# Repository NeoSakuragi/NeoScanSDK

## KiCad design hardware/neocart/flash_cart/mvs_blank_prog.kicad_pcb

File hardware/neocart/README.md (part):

# NeoCart — status 2026-10-01

Single entry point for the cartridge hardware. The 2026-09-23 status further down is kept as history.

## Plan (decided)
- **NeoCart = a platform for homebrews.** Protected commercial games (KOF2000-class: SMA, PVC, PCM2 encryption) are out of scope for now.
- **Flash carts are how games ship; a separate programmer writes them.** The FPGA + RAM cart (NeoSD/Darksoft style) stays a later **dev-cart** track
  (instant reload, bus tracing, breakpoints), not the production cart.
- **Programming is NOT embedded on the cart** (comparison in `progr/DESIGN.md`): ~+$56 per 2-cart order (MCU parts, 6 extended-part fees,
  4 layers), an MCU wired to every flash pin on the live bus, no dump/bench capability. The separate programmer is paid once and doubles as a
  dumper / bench tool, and may be sold later.

## Boards
| Board | Folder | State |
|---|---|---|
| **PROG board v3** (CTRG2) | `pboard/` | Routed, DRC 0/0, Gerbers/BOM/CPL exported. 174 × 134 mm, 2 layers, HASL fingers. P = S29GL064N (8 MB, P1 at MB 7, P2 bank n at MB n, 3-bit latch at $2FFFF0); V = ONE S29GL128P shared by ADPCM-A and ADPCM-B (LVC16374 capture registers as a tri-state mux, break-before-make on /SDPOE). JP1: 1-2 PROGRAM / 2-3 PLAY. Logic sim `sim_pboard.py` 14/14. JLCPCB project "neocart_pboard_jlcpcb": 5 PCBs + 2 assembled = **$94.90** before shipping (real quote). **Not ordered.** |
| **Programmer v1** | `progr/` | Routed, DRC 0/0, exported. 176 × 100 mm, 2 layers. WeAct RP2350B core board on headers + MVS slot (EDAC 345-120-520-201) + 4 × SN74LVC16T245, 74LVC16245A (D bus at 3.3 V), 2 × 74LVC16374 latches, TPS2553 cart switch. Netlist imports the CTRG2 table from `pboard/`; `sim_system.py` runs the firmware cycles against the PROG board netlist (9/9, 6 planted faults caught). Firmware `progr/firmware` (Pico SDK, UF2 in `progr/out`), PC tool `progr/neocart.py`. JLCPCB project "neocart_progr_jlcpcb": 5 PCBs + 2 assembled ≈ **$59** before shipping (built from JLCPCB's own BOM prices; final page not read). Plus module ~$4 and slot ~$14-19 bought separately. **Not ordered.** |
| CHA board | — | Not designed. Reference: KOF96 CHA256 (NEO-273 address latch, NEO-ZMC, 8 × 4 MB C, AT27C010 S1/M1). Will be designed together with programmer v2 (two slots, second WeAct module). |

## Before ordering
1. **Logic-analyzer capture** of /SDROE (A56), /SDPOE (A48), SDRMPX (A55), SDPMPX (A47) on Bruno's MVS with KOF96 playing music: the v3 PROG
   board's one unproven assumption (neogeodev wiki: the two strobes fall together, /SDPOE 250 ns, /SDROE 1.5 µs). Tool: any FX2 "24MHz 8CH"
   USB analyzer (CY7C68013A, sigrok/PulseView), ~€16; the Kingst LA1010 (€72) adds nothing needed here. A probe map (where the four lines run on
   the KOF96 PROG board) is still to be made from the scans.
2. **1:1 paper print** of the PROG board in a real shell (fit).
3. Order both boards in ONE JLCPCB order (one wait, one shipment).
Bring-up order: programmer first, validated by dumping Bruno's own SNK carts against MAME CRCs; then the PROG board, debugged with it.

## Reference hardware
`/data/scans/kof96/` (README + photos): 600 dpi scans and phone photos of KOF96 PROGBK1 and CHA256. PROGBK1 confirms our PROG outline
(holes 90.0 mm apart, 103.7 mm below the top edge) and SNK's own shared-V scheme (SNK PCM 9311 chip, V1-V3 = F32-W1/F32-W2/F16-W3,
P1 = F08-Q1, SP2 = F16-Q2, 74LS74A bank latch). Page: claude.ai/artifact/TCAhpmasqBDWVmgKT9YoJ3.

## Tooling traps found 2026-10-01 (see also ../CLAUDE.md)
- `pcbnew` `board.Save()` rewrites the `.kicad_pro` next to the board with KiCad's default net class (0.2 mm): write project rules AFTER saving.
- Freerouting ignores copper-to-edge clearance: add 0.45 mm no-track bands inside every edge before routing.
- A fine-pitch QFN needs a free ring (≥ 2-3 mm) or the autorouter boxes its pins in; a chip module removes the problem.
- Pre-route straight links (latch → shifter) as locked tracks, and gate them against every pad: one pass shorted through decoupling caps.
- KiCad's DRC reports a disconnected ground island only as "zone ↔ zone" at the zone origin; find it with a fragment graph
  (vias, pads, tracks joining filled-polygon fragments). One such island left two GND pins of a level shifter floating.
- `pkill -f <pattern>` matches its own shell: use `pgrep -f "patter[n]"` + kill by PID.
- Shared drivers: `pboard/route_pboard.py` (ROUTE_DIR/ROUTE_NAME), `export_pboard.py` (EXPORT_DIR/EXPORT_NAME), `price_bom.py` (PRICE_DIR),
  `pour_pboard.py` (POUR_YMAX) serve both boards.

# History: status 2026-09-23

Restarted after a four-month gap. This file is the single entry point; the per-track docs below are older and partly superseded.

## What exists
| Track | State |
|---|---|
| v4 PROG + CHA adapters (`adapter/`, JLCPCB order W202604300512O366, 2026-04-30) | On the bench. Header mirrored, holes don't match the shell, no gold fingers, and a design flaw: 74HC165 shift-register address capture (~1 µs) can never meet the 68K's ~150 ns P-ROM window. **Written off.** |
| QMTech XC7A100T core + DB_FPGA_with_RP2040 daughter (ordered 2026-04-28) | Owned, never programmed. No Verilog exists for it (`fpga/rtl` targets the ECP5 board). |
| ECP5-25F custom board (`fpga/`, `HANDOFF_FINAL.md`) | Shelved: superseded by the QMTech route. |
| Flash cart spec (`FLASH_CART_DESIGN.md`, `FLASH_CART_RESEARCH.md`) | Architecture and BOM only; nothing built. 5 V parts in it are no longer sourceable. |
| Blank MVS boards + P-ROM breakout (`flash_cart/`, last commit 2026-05-18) | Routing unfinished; unknown whether the blank PROG board was ever ordered. |

## Target (Bruno, 2026-09-23)
Two PCBs, install the QMTech, drop into donor shells: a playable cart with connectivity (USB, microSD) and debug (bus snooping, breakpoints). Assessment: correct topology, identical to NeoSD / Darksoft, with one correction — the FPGA maps, programs and watches the buses; the ROM data lives in memory chips on the bus.

## Constraints
**Pin budget** (from `adapter/gen_both_pcbs.py` net lists, derived from the diag carts and jamma-nation-x):

| | Signals |
|---|---|
| CTRG2 (PROG): D0–15, A1–19, control incl. ROMWAIT/PWAIT/PDTACK, ADPCM buses | 84 |
| CTRG1 (CHA): CR0–31, P0–23, SDA0–15, SDD0–7, FIX0–7, clocks/ctrl | 99 |
| Total | 183 |
| QMTech IOs on its two headers | 108 |

One QMTech cannot even tap both boards. Options: one QMTech per board (216 IOs, +€74, recommended) or QMTech on PROG only with the CHA as a flash board programmed over a slow serial link (no graphics-bus snooping).

**Timing** (neogeodev wiki): 68K user RAM is 100 ns parts, 166 ns window at 12 MHz → P-ROM ≈ 150 ns. C-ROM address latched by PCK1B (low 55 ns, high 610 ns, 1.5 MHz) → ≈ 600 ns per fetch. XC7A100T BRAM = 607 KB; DDR3 via MIG is too slow for P. Hence NOR flash (S29GL064N, 90 ns) or SRAM for P directly on the bus behind SN74LVC16245 shifters; the FPGA taps the 3.3 V side, drives bank bits and chip enables, programs the flash in-system through the CFI command set, and, for breakpoints, can disable the flash output and drive an instruction onto the data bus (ROMWAIT/PWAIT only configure fixed wait states; they cannot stall the 68K).

**QMTech physical facts** (manual, `datasheets/`): 84.1 × 67.1 mm; two 2×32 female headers on the underside, rows 61 mm apart, 4.1 mm from the edge, pins 1/2 at the left end in top view; U4 = banks 34/35 (1–2 VCCO, 59–64 VIN), U2 = banks 13/14/15 (1–2 3V3, 59–64 VIN); own 5 V DC jack; 6-pin JTAG; N25Q64A config flash. The RP2040 daughter plugs into the same female headers, so it cannot share the core with the cart adapter: the adapter carries its own microSD slot and USB-serial chip; the FPGA is programmed over JTAG into the config flash.

**Sourcing, JLCPCB API 2026-09-23:**

| Part | Role | Price | Stock |
|---|---|---|---|
| S29GL064N90TFI040, 8 MB, 3.3 V, 90 ns | every ROM | $4.65 | 108 |
| IS62WV51216BLL-55TLI, 1 MB SRAM, 55 ns | instant-reload P-ROM option | $12.02 | 4023 |
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
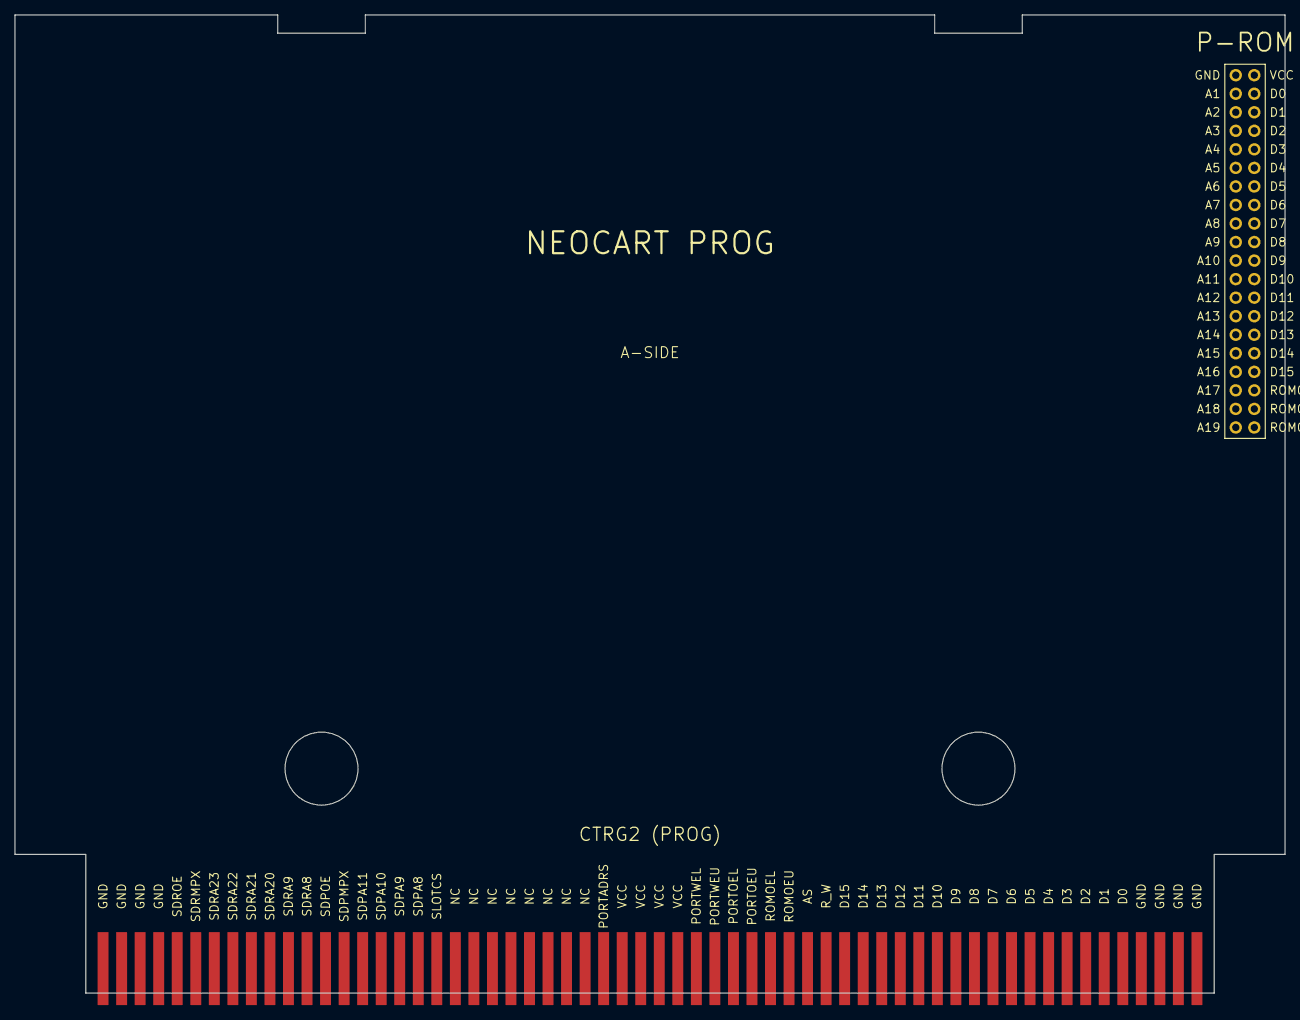
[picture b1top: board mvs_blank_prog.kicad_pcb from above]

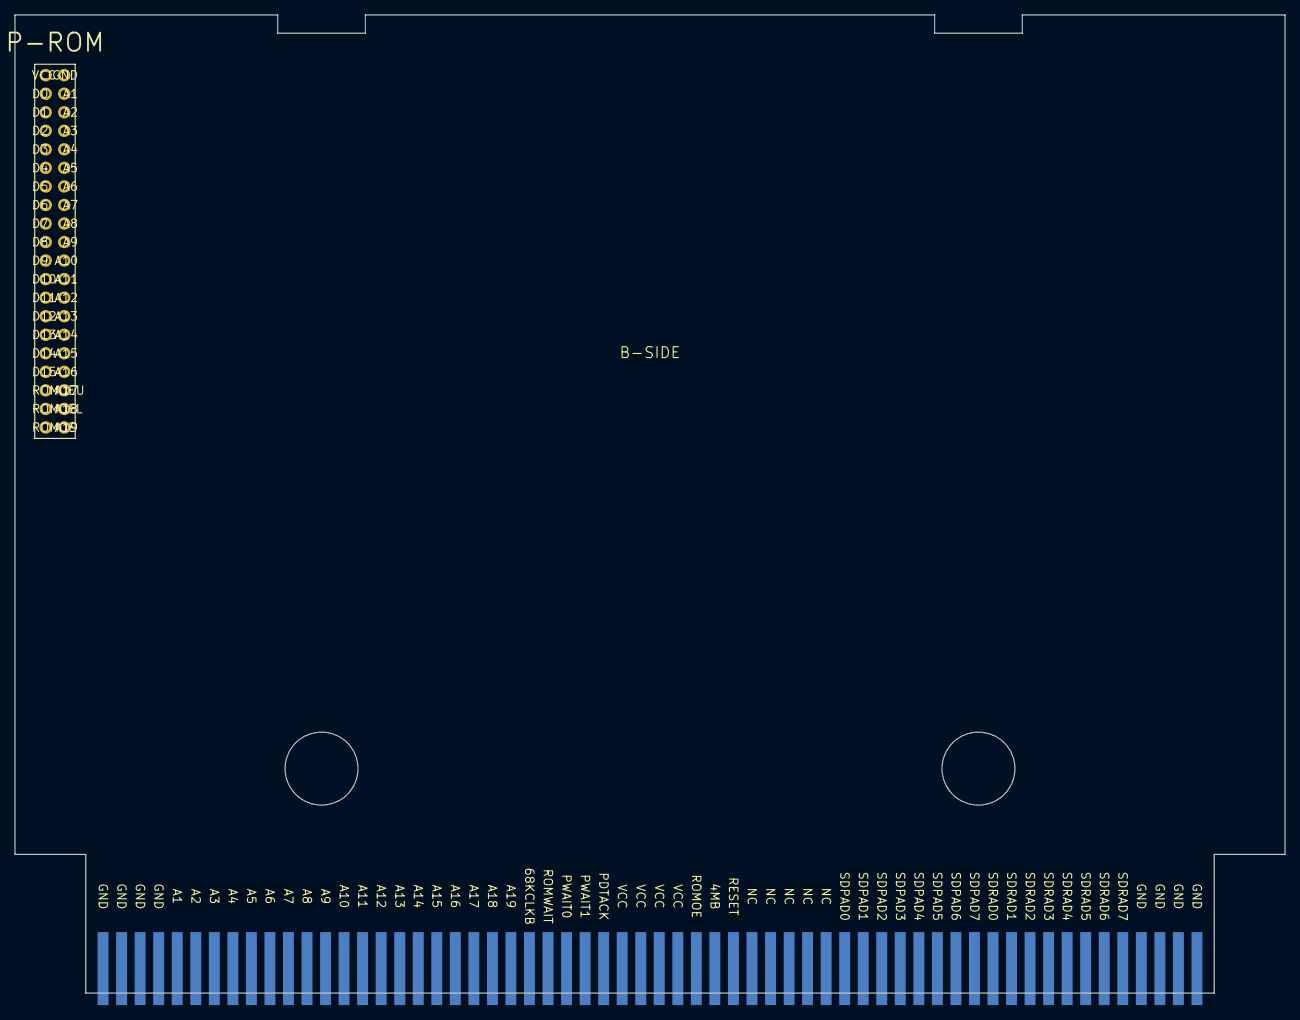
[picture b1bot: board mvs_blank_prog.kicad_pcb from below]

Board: 2 copper layers, 174.0 x 134.0 mm, 121 parts (60 on the bottom side), 40 nets, no tracks yet.

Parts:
A1, A2, A3, A4, A57, A58, A59, A60: GND
A5: D0
A6: D1
A7: D2
A8: D3
A9: D4
A10: D5
A11: D6
A12: D7
A13: D8
A14: D9
A15: D10
A16: D11
A17: D12
A18: D13
A19: D14
A20: D15
A21: R_W
A22: AS
A23: ROMOEU
A24: ROMOEL
A25: PORTOEU
A26: PORTOEL
A27: PORTWEU
A28: PORTWEL
A29, A30, A31, A32: VCC
A33: PORTADRS
A34, A35, A36, A37, A38, A39, A40, A41: NC
A42: SLOTCS
A43: SDPA8
A44: SDPA9
A45: SDPA10
A46: SDPA11
A47: SDPMPX
A48: SDPOE
A49: SDRA8
A50: SDRA9
A51: SDRA20
A52: SDRA21
A53: SDRA22
A54: SDRA23
A55: SDRMPX
A56: SDROE
B1, B2, B3, B4, B57, B58, B59, B60: GND
B5: A1
B6: A2
B7: A3
B8: A4
B9: A5
B10: A6
B11: A7
B12: A8
B13: A9
B14: A10
B15: A11
B16: A12
B17: A13
B18: A14
B19: A15
B20: A16
B21: A17
B22: A18
B23: A19
B24: 68KCLKB
B25: ROMWAIT
B26: PWAIT0
B27: PWAIT1
B28: PDTACK
B29, B30, B31, B32: VCC
B33: ROMOE
B34: 4MB
B35: RESET
B36, B37, B38, B39, B40: NC
B41: SDPAD0
B42: SDPAD1
B43: SDPAD2
B44: SDPAD3
B45: SDPAD4
B46: SDPAD5
B47: SDPAD6
B48: SDPAD7
B49: SDRAD0
B50: SDRAD1
B51: SDRAD2
B52: SDRAD3
B53: SDRAD4
B54: SDRAD5
B55: SDRAD6
B56: SDRAD7
J_PROM: P-ROM 2x20

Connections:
A1: B5.1, J_PROM.3
A2: B6.1, J_PROM.5
A3: B7.1, J_PROM.7
A4: B8.1, J_PROM.9
A5: B9.1, J_PROM.11
A6: B10.1, J_PROM.13
A7: B11.1, J_PROM.15
A8: B12.1, J_PROM.17
A9: B13.1, J_PROM.19
A10: B14.1, J_PROM.21
A11: B15.1, J_PROM.23
A12: B16.1, J_PROM.25
A13: B17.1, J_PROM.27
A14: B18.1, J_PROM.29
A15: B19.1, J_PROM.31
A16: B20.1, J_PROM.33
A17: B21.1, J_PROM.35
A18: B22.1, J_PROM.37
A19: B23.1, J_PROM.39
D0: A5.1, J_PROM.4
D1: A6.1, J_PROM.6
D2: A7.1, J_PROM.8
D3: A8.1, J_PROM.10
D4: A9.1, J_PROM.12
D5: A10.1, J_PROM.14
D6: A11.1, J_PROM.16
D7: A12.1, J_PROM.18
D8: A13.1, J_PROM.20
D9: A14.1, J_PROM.22
D10: A15.1, J_PROM.24
D11: A16.1, J_PROM.26
D12: A17.1, J_PROM.28
D13: A18.1, J_PROM.30
D14: A19.1, J_PROM.32
D15: A20.1, J_PROM.34
GND: B1.1, J_PROM.1
ROMOE: B33.1, J_PROM.40
ROMOEL: A24.1, J_PROM.38
ROMOEU: A23.1, J_PROM.36
VCC: A29.1, J_PROM.2

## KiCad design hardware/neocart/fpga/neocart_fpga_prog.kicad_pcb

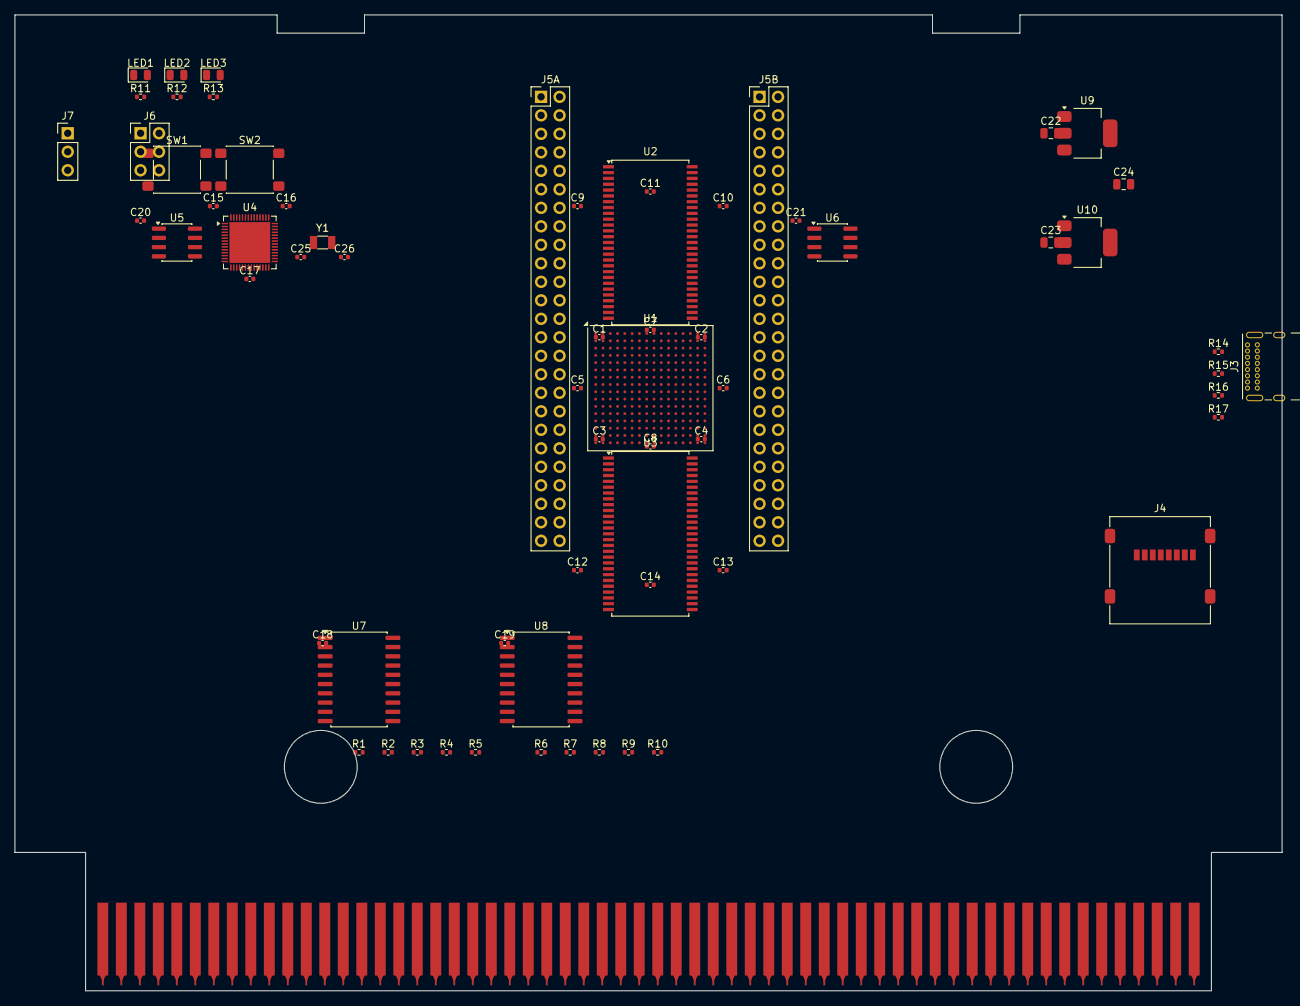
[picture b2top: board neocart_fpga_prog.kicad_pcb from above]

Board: 4 copper layers, 174.0 x 134.0 mm, 67 parts (1 on the bottom side), 93 nets, no tracks yet.

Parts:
C1, C2, C3, C4, C5, C6, C7, C8, C9, C10, C11, C12, C13, C14, C15, C16, C17, C18, C19, C20, C21: 100nF; C_0402_1005Metric
C22, C23, C24: 10uF; C_0805_2012Metric
C25, C26: 22pF; C_0402_1005Metric
J1: NeoGeo MVS Prog B Side Edge; neogeo-mvs-prog-b-side-edge
J2: NeoGeo MVS Prog A Side Edge; neogeo-mvs-prog-a-side-edge
J3: USB-C; USB_C_Receptacle_GCT_USB4085
J4: microSD; microSD_HC_Molex_47219-2001
J5A: InterBoard-A 2x25; PinHeader_2x25_P2.54mm_Vertical
J5B: InterBoard-B 2x25; PinHeader_2x25_P2.54mm_Vertical
J6: JTAG; PinHeader_2x03_P2.54mm_Vertical
J7: UART; PinHeader_1x03_P2.54mm_Vertical
LED1: PWR Green; LED_0805_2012Metric
LED2: ACT Yellow; LED_0805_2012Metric
LED3: USR Red; LED_0805_2012Metric
R1, R2, R3, R4, R5, R6, R7, R8, R9, R10: 33R; R_0402_1005Metric
R11, R12, R13: 1K; R_0402_1005Metric
R14: 5.1K CC1; R_0402_1005Metric
R15: 5.1K CC2; R_0402_1005Metric
R16: 27R D+; R_0402_1005Metric
R17: 27R D-; R_0402_1005Metric
SW1: BOOTSEL; SW_SPST_PTS645Sx43SMTR92
SW2: RESET; SW_SPST_PTS645Sx43SMTR92
U1: ECP5-25F BGA256; BGA-256_17.0x17.0mm_Layout16x16_P1.0mm_Ball0.5mm_Pad0.4mm_N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
U2, U3: IS42S16160J SDRAM; TSOP-II-54_22.2x10.16mm_P0.8mm
U4: RP2040; QFN-56-1EP_7x7mm_P0.4mm_EP5.6x5.6mm
U5: W25Q32JVS RP2040-Flash; SOIC-8_3.9x4.9mm_P1.27mm
U6: W25Q32JVS FPGA-Config; SOIC-8_3.9x4.9mm_P1.27mm
U7, U8: 74LVC245A Bus-Xcvr; SOIC-20W_7.5x12.8mm_P1.27mm
U9: AMS1117-3.3; SOT-223-3_TabPin2
U10: AMS1117-1.1; SOT-223-3_TabPin2
Y1: 12MHz; Crystal_SMD_3215-2Pin_3.2x1.5mm

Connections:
GND: C1.2, C2.2, C3.2, C4.2, C5.2, C6.2, C7.2, C8.2, C9.2, C10.2, C11.2, C12.2, C13.2, C14.2, C15.2, C16.2, C17.2, C18.2, C19.2, C20.2, C21.2, C22.2, C23.2, C24.2, C25.2, C26.2, J1.1 (GND), J1.2 (GND), J1.3 (GND), J1.4 (GND), J1.58 (GND), J1.59 (GND), J1.60 (GND), J2.1 (GND), J2.2 (GND), J2.3 (GND), J2.4 (GND), J2.58 (GND), J2.59 (GND), J2.60 (GND), J3.A1, J3.A12, J3.B1, J3.B12, J3.S1, J4.3, J4.6, J4.9, J6.2, J7.3, LED1.2, LED2.2, LED3.2, R14.2, R15.2, SW1.2, SW2.2, U2.27, U2.28, U2.43, U2.49, U3.27, U3.28, U3.43, U3.49, U4.19, U4.57, U5.4, U6.4, U7.10, U8.10, U9.1, U10.1
PA0: J1.5 (A1), R1.1
PA1: J1.6 (A2), R2.1
PA2: J1.7 (A3), R3.1
PA3: J1.8 (A4), R4.1
PA4: J1.9 (A5), R5.1
PA5: J1.10 (A6), R6.1
PA6: J1.11 (A7), R7.1
PA7: J1.12 (A8), R8.1
PD0: J2.5 (D0), U7.2
PD1: J2.6 (D1), U7.3
PD2: J2.7 (D2), U7.4
PD3: J2.8 (D3), U7.5
PD4: J2.9 (D4), U7.6
PD5: J2.10 (D5), U7.7
PD6: J2.11 (D6), U7.8
PD7: J2.12 (D7), U7.9
PD8: J2.13 (D8), U8.2
PD9: J2.14 (D9), U8.3
PD10: J2.15 (D10), U8.4
PD11: J2.16 (D11), U8.5
PD12: J2.17 (D12), U8.6
PD13: J2.18 (D13), U8.7
PD14: J2.19 (D14), U8.8
PD15: J2.20 (D15), U8.9
ROMOE: J2.33 (PORTADRS), R10.1
RP_DVDD: U4.23, U4.45, U4.56
RP_GPIO8: R1.2, U4.11
RP_GPIO9: R2.2, U4.12
RP_GPIO10: R3.2, U4.13
RP_GPIO11: R4.2, U4.14
RP_GPIO12: R5.2, U4.15
RP_GPIO13: R6.2, U4.16
RP_GPIO14: R7.2, U4.17
RP_GPIO15: R8.2, U4.18
RP_GPIO16: R9.2, U4.27
RP_GPIO17: R10.2, U4.28
RP_USB_DM: R17.2, U4.46
RP_USB_DP: R16.2, U4.47
SDRAM_A0: U2.16, U3.16
SDRAM_A1: U2.17, U3.17
SDRAM_A2: U2.18, U3.18
SDRAM_A3: U2.19, U3.19
SDRAM_A4: U2.20, U3.20
SDRAM_A5: U2.21, U3.21
SDRAM_A6: U2.22, U3.22
SDRAM_A7: U2.23, U3.23
SDRAM_A8: U2.25, U3.25
SDRAM_A9: U2.26, U3.26
SDRAM_A10: U2.15, U3.15
SDRAM_A11: U2.29, U3.29
SDRAM_A12: U2.30, U3.30
SDRAM_BA0: U2.13, U3.13
SDRAM_BA1: U2.14, U3.14
SDRAM_CASN: U2.10, U3.10
SDRAM_CKE: U2.33, U3.33
SDRAM_CLK: U2.32, U3.32
SDRAM_DQ0: U2.3, U3.3
SDRAM_DQ1: U2.4, U3.4
SDRAM_DQ2: U2.5, U3.5
SDRAM_DQ3: U2.6, U3.6
SDRAM_DQ4: U2.38, U3.38
SDRAM_DQ5: U2.39, U3.39
SDRAM_DQ6: U2.40, U3.40
SDRAM_DQ7: U2.41, U3.41
SDRAM_DQ8: U2.44, U3.44
SDRAM_DQ9: U2.45, U3.45
SDRAM_DQ10: U2.46, U3.46
SDRAM_DQ11: U2.47, U3.47
SDRAM_DQ12: U2.50, U3.50
SDRAM_DQ13: U2.51, U3.51
SDRAM_DQ14: U2.52, U3.52
SDRAM_DQ15: U2.53, U3.53
SDRAM_DQM0: U2.8, U3.8
SDRAM_DQM1: U2.34, U3.34
SDRAM_RASN: U2.11, U3.11
SDRAM_WEN: U2.9, U3.9
SDROE: J1.56 (SDRAD7), J2.56 (SDROE)
SD_CD: LED1.1, R11.2
SD_D2: C26.1, Y1.2
SD_D3: LED3.1, R13.2
SD_VDD: LED2.1, R12.2
USB_CC1: J3.A5, R14.1
USB_CC2: J3.B5, R15.1
USB_DM: J3.A7, J3.B7, R17.1
USB_DP: J3.A6, J3.B6, R16.1
USB_VBUS: J3.A4, J3.A9, J3.B4, J3.B9
VCC_3V3: C1.1, C2.1, C3.1, C4.1, C5.1, C6.1, C7.1, C8.1, C9.1, C10.1, C11.1, C12.1, C13.1, C14.1, C15.1, C16.1, C17.1, C20.1, C21.1, C23.1, C24.1, J4.4, J6.4, R11.1, R12.1, R13.1, U2.1, U2.2, U2.7, U2.24, U2.31, U2.42, U2.48, U2.54, U3.1, U3.2, U3.7, U3.24, U3.31, U3.42, U3.48, U3.54, U4.1, U4.10, U4.22, U4.33, U4.42, U4.43, U4.44, U4.48, U4.55, U5.8, U6.8, U9.2, U10.3
VCC_5V: C18.1, C19.1, C22.1, J1.29 (VCC), J1.30 (VCC), J1.31 (VCC), J1.32 (VCC), J2.29 (VCC), J2.30 (VCC), J2.31 (VCC), J2.32 (VCC), U7.20, U8.20, U9.3
XCVR_DIR: U7.1, U8.1
XCVR_OE: U7.19, U8.19
nRESET: C25.1, Y1.1
nRW: J2.21 (R/W), R9.1

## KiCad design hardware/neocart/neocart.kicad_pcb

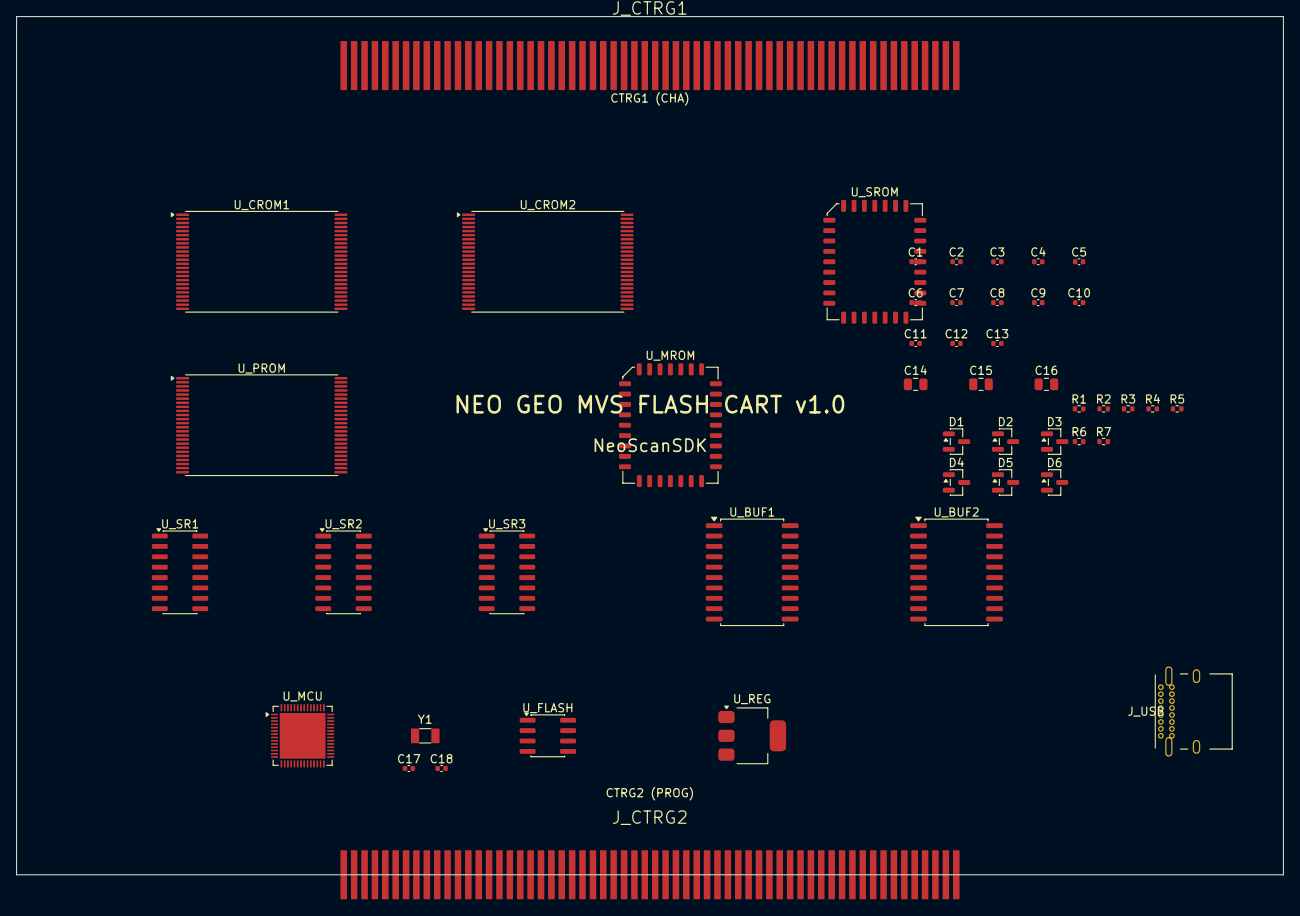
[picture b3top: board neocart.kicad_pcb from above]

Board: 4 copper layers, 155.0 x 105.0 mm, 48 parts (0 on the bottom side), 174 nets, no tracks yet.

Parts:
C1, C2, C3, C4, C5, C6, C7, C8, C9, C10, C11, C12, C13: 100nF; C_0402_1005Metric
C14, C15, C16: 10uF; C_0805_2012Metric
C17, C18: 15pF; C_0402_1005Metric
D1, D2, D3, D4, D5, D6: BAT54S; SOT-23
J_CTRG1: CTRG1_CHA; J_CTRG1
J_CTRG2: CTRG2_PROG; J_CTRG2
J_USB: USB_C; USB_C_Receptacle_GCT_USB4085
R1: 1K; R_0402_1005Metric
R2, R3: 27R; R_0402_1005Metric
R4, R5: 5.1K; R_0402_1005Metric
R6, R7: 10K; R_0402_1005Metric
U_BUF1: 74HC245_DATA; SOIC-20W_7.5x12.8mm_P1.27mm
U_BUF2: 74HC245_CTRL; SOIC-20W_7.5x12.8mm_P1.27mm
U_CROM1: AM29F400_C1; TSOP-I-48_18.4x12mm_P0.5mm
U_CROM2: AM29F400_C2; TSOP-I-48_18.4x12mm_P0.5mm
U_FLASH: W25Q32; SOIC-8_3.9x4.9mm_P1.27mm
U_MCU: RP2040; QFN-56-1EP_7x7mm_P0.4mm_EP5.6x5.6mm
U_MROM: SST39SF010_M; PLCC-32_11.4x14.0mm_P1.27mm
U_PROM: AM29F400_P; TSOP-I-48_18.4x12mm_P0.5mm
U_REG: AMS1117-3.3; SOT-223-3_TabPin2
U_SR1, U_SR2, U_SR3: 74HC595; SOIC-16_3.9x9.9mm_P1.27mm
U_SROM: SST39SF010_S; PLCC-32_11.4x14.0mm_P1.27mm
Y1: 12MHz; Crystal_SMD_3215-2Pin_3.2x1.5mm

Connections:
BUF_nOE: U_BUF1.19, U_BUF2.19, U_MCU.23
BUS_DIR: U_BUF1.1, U_BUF2.1, U_MCU.21
CA0: J_CTRG1.A3, U_CROM1.25, U_CROM2.25
CA1: J_CTRG1.B3, U_CROM1.24, U_CROM2.24
CA2: J_CTRG1.A4, U_CROM1.23, U_CROM2.23
CA3: J_CTRG1.B4, U_CROM1.22, U_CROM2.22
CA4: J_CTRG1.A5, U_CROM1.21, U_CROM2.21
CA5: J_CTRG1.B5, U_CROM1.20, U_CROM2.20
CA6: J_CTRG1.A6, U_CROM1.19, U_CROM2.19
CA7: J_CTRG1.B6, U_CROM1.18, U_CROM2.18
CA8: J_CTRG1.A7, U_CROM1.8, U_CROM2.8
CA9: J_CTRG1.B7, U_CROM1.7, U_CROM2.7
CA10: J_CTRG1.A8, U_CROM1.6, U_CROM2.6
CA11: J_CTRG1.B8, U_CROM1.5, U_CROM2.5
CA12: J_CTRG1.A9, U_CROM1.4, U_CROM2.4
CA13: J_CTRG1.B9, U_CROM1.3, U_CROM2.3
CA14: J_CTRG1.A10, U_CROM1.2, U_CROM2.2
CA15: J_CTRG1.B10, U_CROM1.1, U_CROM2.1
CA16: J_CTRG1.A11, U_CROM1.48, U_CROM2.48
CA17: J_CTRG1.B11, U_CROM1.47, U_CROM2.47
CR0: J_CTRG1.A19, U_CROM1.29
CR1: J_CTRG1.B19, U_CROM1.31
CR2: J_CTRG1.A20, U_CROM1.33
CR3: J_CTRG1.B20, U_CROM1.35
CR4: J_CTRG1.A21, U_CROM1.38
CR5: J_CTRG1.B21, U_CROM1.40
CR6: J_CTRG1.A22, U_CROM1.42
CR7: J_CTRG1.B22, U_CROM1.44
CR8: J_CTRG1.A23, U_CROM1.30
CR9: J_CTRG1.B23, U_CROM1.32
CR10: J_CTRG1.A24, U_CROM1.34
CR11: J_CTRG1.B24, U_CROM1.36
CR12: J_CTRG1.A25, U_CROM1.39
CR13: J_CTRG1.B25, U_CROM1.41
CR14: J_CTRG1.A26, U_CROM1.43
CR15: J_CTRG1.B26, U_CROM1.45
CR16: J_CTRG1.A27, U_CROM2.29
CR17: J_CTRG1.B27, U_CROM2.31
CR18: J_CTRG1.A28, U_CROM2.33
CR19: J_CTRG1.B28, U_CROM2.35
CR20: J_CTRG1.A33, U_CROM2.38
CR21: J_CTRG1.B33, U_CROM2.40
CR22: J_CTRG1.A34, U_CROM2.42
CR23: J_CTRG1.B34, U_CROM2.44
CR24: J_CTRG1.A35, U_CROM2.30
CR25: J_CTRG1.B35, U_CROM2.32
CR26: J_CTRG1.A36, U_CROM2.34
CR27: J_CTRG1.B36, U_CROM2.36
CR28: J_CTRG1.A37, U_CROM2.39
CR29: J_CTRG1.B37, U_CROM2.41
CR30: J_CTRG1.A38, U_CROM2.43
CR31: J_CTRG1.B38, U_CROM2.45
GND: J_CTRG1.A1, J_CTRG1.A2, J_CTRG1.A17, J_CTRG1.A18, J_CTRG1.A39, J_CTRG1.A40, J_CTRG1.A41, J_CTRG1.A42, J_CTRG1.A58, J_CTRG1.A59, J_CTRG1.A60, J_CTRG1.B1, J_CTRG1.B2, J_CTRG1.B15, J_CTRG1.B16, J_CTRG1.B17, J_CTRG1.B18, J_CTRG1.B39, J_CTRG1.B40, J_CTRG1.B41, J_CTRG1.B42, J_CTRG1.B43, J_CTRG1.B44, J_CTRG1.B45, J_CTRG1.B46, J_CTRG1.B58, J_CTRG1.B59, J_CTRG1.B60, J_CTRG2.A1, J_CTRG2.A2, J_CTRG2.A3, J_CTRG2.A4, J_CTRG2.A21, J_CTRG2.A22, J_CTRG2.A25, J_CTRG2.A26, J_CTRG2.A27, J_CTRG2.A28, J_CTRG2.A34, J_CTRG2.A35, J_CTRG2.A36, J_CTRG2.A37, J_CTRG2.A38, J_CTRG2.A39, J_CTRG2.A40, J_CTRG2.A41, J_CTRG2.A42, J_CTRG2.A43, J_CTRG2.A44, J_CTRG2.A45, J_CTRG2.A46, J_CTRG2.A56, J_CTRG2.A57, J_CTRG2.A58, J_CTRG2.A59, J_CTRG2.A60, J_CTRG2.B1, J_CTRG2.B2, J_CTRG2.B3, J_CTRG2.B4, J_CTRG2.B23, J_CTRG2.B24, J_CTRG2.B25, J_CTRG2.B26, J_CTRG2.B27, J_CTRG2.B28, J_CTRG2.B33, J_CTRG2.B34, J_CTRG2.B35, J_CTRG2.B36, J_CTRG2.B37, J_CTRG2.B38, J_CTRG2.B39, J_CTRG2.B57, J_CTRG2.B58, J_CTRG2.B59, J_CTRG2.B60, U_BUF1.10, U_BUF2.10, U_CROM1.27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
MA0: J_CTRG2.B48, U_MROM.12
MA1: J_CTRG2.B49, U_MROM.11
MA2: J_CTRG2.B50, U_MROM.10
MA3: J_CTRG2.B51, U_MROM.9
MA4: J_CTRG2.B52, U_MROM.8
MA5: J_CTRG2.B53, U_MROM.7
MA6: J_CTRG2.B54, U_MROM.6
MA7: J_CTRG2.B55, U_MROM.5
MA8: J_CTRG2.A47, U_MROM.27
MA9: J_CTRG2.A48, U_MROM.26
MA10: J_CTRG2.A49, U_MROM.23
MA11: J_CTRG2.A50, U_MROM.25
MA12: J_CTRG2.A51, U_MROM.4
MA13: J_CTRG2.A52, U_MROM.28
MA14: J_CTRG2.A53, U_MROM.29
MA15: J_CTRG2.A54, U_MROM.3
MA16: J_CTRG2.A55, U_MROM.2
MD0: J_CTRG2.B40, U_MROM.13
MD1: J_CTRG2.B41, U_MROM.14
MD2: J_CTRG2.B42, U_MROM.15
MD3: J_CTRG2.B43, U_MROM.17
MD4: J_CTRG2.B44, U_MROM.18
MD5: J_CTRG2.B45, U_MROM.19
MD6: J_CTRG2.B46, U_MROM.20
MD7: J_CTRG2.B47, U_MROM.21
PA0: J_CTRG2.B5, U_PROM.25
PA1: J_CTRG2.B6, U_PROM.24
PA2: J_CTRG2.B7, U_PROM.23
PA3: J_CTRG2.B8, U_PROM.22
PA4: J_CTRG2.B9, U_PROM.21
PA5: J_CTRG2.B10, U_PROM.20
PA6: J_CTRG2.B11, U_PROM.19
PA7: J_CTRG2.B12, U_PROM.18
PA8: J_CTRG2.B13, U_PROM.8
PA9: J_CTRG2.B14, U_PROM.7
PA10: J_CTRG2.B15, U_PROM.6
PA11: J_CTRG2.B16, U_PROM.5
PA12: J_CTRG2.B17, U_PROM.4
PA13: J_CTRG2.B18, U_PROM.3
PA14: J_CTRG2.B19, U_PROM.2
PA15: J_CTRG2.B20, U_PROM.1
PA16: J_CTRG2.B21, U_PROM.48
PA17: J_CTRG2.B22, U_PROM.47
PD0: J_CTRG2.A5, U_PROM.29
PD1: J_CTRG2.A6, U_PROM.31
PD2: J_CTRG2.A7, U_PROM.33
PD3: J_CTRG2.A8, U_PROM.35
PD4: J_CTRG2.A9, U_PROM.38
PD5: J_CTRG2.A10, U_PROM.40
PD6: J_CTRG2.A11, U_PROM.42
PD7: J_CTRG2.A12, U_PROM.44
PD8: J_CTRG2.A13, U_PROM.30
PD9: J_CTRG2.A14, U_PROM.32
PD10: J_CTRG2.A15, U_PROM.34
PD11: J_CTRG2.A16, U_PROM.36
PD12: J_CTRG2.A17, U_PROM.39
PD13: J_CTRG2.A18, U_PROM.41
PD14: J_CTRG2.A19, U_PROM.43
PD15: J_CTRG2.A20, U_PROM.45
PRGD0: U_BUF1.2, U_BUF1.18, U_MCU.5
PRGD1: U_BUF1.3, U_BUF1.17, U_MCU.6
PRGD2: U_BUF1.4, U_BUF1.16, U_MCU.7
PRGD3: U_BUF1.5, U_BUF1.15, U_MCU.8
PRGD4: U_BUF1.6, U_BUF1.14, U_MCU.9
PRGD5: U_BUF1.7, U_BUF1.13, U_MCU.10
PRGD6: U_BUF1.8, U_BUF1.12, U_MCU.11
PRGD7: U_BUF1.9, U_BUF1.11, U_MCU.12
PROG_nBYTE: U_BUF2.9, U_MCU.20
PROG_nCE_C1: U_BUF2.5, U_MCU.18
PROG_nCE_C2: U_BUF2.6, U_MCU.19
PROG_nCE_M: U_BUF2.4, U_MCU.17
PROG_nCE_P: U_BUF2.2, U_MCU.15
PROG_nCE_S: U_BUF2.3, U_MCU.16
PROG_nOE: U_BUF2.8, U_MCU.14
PROG_nWE: U_BUF2.7, U_MCU.13
QSPI_SCLK: U_FLASH.6, U_MCU.37
QSPI_SD0: U_FLASH.5, U_MCU.38
QSPI_SD1: U_FLASH.2, U_MCU.39
QSPI_SS: U_FLASH.1, U_MCU.36
SA0: J_CTRG1.A43, U_SROM.12
SA1: J_CTRG1.A44, U_SROM.11
SA2: J_CTRG1.A45, U_SROM.10
SA3: J_CTRG1.A46, U_SROM.9
SA4: J_CTRG1.A47, U_SROM.8
SA5: J_CTRG1.A48, U_SROM.7
SA6: J_CTRG1.A49, U_SROM.6
SA7: J_CTRG1.A50, U_SROM.5
SA8: J_CTRG1.A51, U_SROM.27
SA9: J_CTRG1.A52, U_SROM.26
SA10: J_CTRG1.A53, U_SROM.23
SA11: J_CTRG1.A54, U_SROM.25
SA12: J_CTRG1.A55, U_SROM.4
SA13: J_CTRG1.A56, U_SROM.28
SA14: J_CTRG1.A57, U_SROM.29
SA15: J_CTRG1.B57, U_SROM.3
SD0: J_CTRG1.B48, U_SROM.13
SD1: J_CTRG1.B49, U_SROM.14
SD2: J_CTRG1.B50, U_SROM.15
SD3: J_CTRG1.B51, U_SROM.17
SD4: J_CTRG1.B52, U_SROM.18
SD5: J_CTRG1.B53, U_SROM.19
SD6: J_CTRG1.B54, U_SROM.20
SD7: J_CTRG1.B55, U_SROM.21
SR_CHAIN_0: U_SR1.9, U_SR2.14
SR_CHAIN_1: U_SR2.9, U_SR3.14
SR_RCLK: U_MCU.4, U_SR1.12, U_SR2.12, U_SR3.12
SR_SER: U_MCU.2, U_SR1.14
SR_SRCLK: U_MCU.3, U_SR1.11, U_SR2.11, U_SR3.11
SR_nOE: U_MCU.22, U_SR1.13, U_SR2.13, U_SR3.13
VCC_3V3: U_FLASH.3, U_FLASH.7, U_FLASH.8, U_MCU.1, U_MCU.44, U_MCU.45, U_MCU.46, U_MCU.47, U_MCU.48, U_MCU.49, U_MCU.50, U_MCU.51, U_MCU.52, U_MCU.53, U_MCU.54, U_MCU.55, U_REG.2, U_SR1.10, U_SR1.16, U_SR2.10, U_SR2.16, U_SR3.10, U_SR3.16
VCC_5V: J_CTRG1.A29, J_CTRG1.A30, J_CTRG1.A31, J_CTRG1.A32, J_CTRG1.B29, J_CTRG1.B30, J_CTRG1.B31, J_CTRG1.B32, J_CTRG2.A29, J_CTRG2.A30, J_CTRG2.A31, J_CTRG2.A32, J_CTRG2.B29, J_CTRG2.B30, J_CTRG2.B31, J_CTRG2.B32, U_BUF1.20, U_BUF2.20, U_CROM1.12, U_CROM2.12, U_MROM.32, U_PROM.12, U_PROM.46, U_REG.3, U_SROM.32
XIN: U_MCU.42, Y1.1
XOUT: U_MCU.43, Y1.2
nBYTE_FLASH: U_BUF2.11, U_CROM1.11, U_CROM2.11, U_PROM.11
nCE_C1: U_BUF2.15, U_CROM1.17
nCE_C2: U_BUF2.14, U_CROM2.17
nCE_M: U_BUF2.16, U_MROM.22
nCE_P: U_BUF2.18, U_PROM.17
nCE_S: U_BUF2.17, U_SROM.22
nOE_P: U_BUF2.12, U_PROM.26
nWE_P: U_BUF2.13, U_PROM.28

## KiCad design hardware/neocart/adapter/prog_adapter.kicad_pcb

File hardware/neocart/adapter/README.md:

> **Warning (2026-09-23):** the v4 boards below were fabricated but cannot serve ROMs in real time — the 74HC165 shift-register address capture takes ~1 µs against the 68K's ~150 ns P-ROM window. They also have a mirrored FPGA header, wrong shell holes and no gold fingers. Written off; see `../README.md`.

# NeoCart PCB Adapters

KiCad PCB designs for PROG and CHA board adapters that connect an FPGA to the MVS cart slot.

## Current Designs

### PROG Board (v5 TQFP)
68K program bus adapter. Connects to CTRG2 (PROG connector).
- `prog_v5_tqfp.kicad_pcb` — unrouted
- `prog_v5_tqfp_routed.kicad_pcb` — autorouted

### PROG Breakout
Simpler breakout board for prototyping.
- `prog_breakout.kicad_pcb` — unrouted
- `prog_breakout_routed.kicad_pcb` — autorouted

### CHA Board (v5 TQFP)
Character/sound bus adapter. Connects to CTRG1 (CHA connector).
- `cha_v5_tqfp.kicad_pcb` — unrouted
- `cha_v5_tqfp_routed.kicad_pcb` — autorouted

## Production Files

- `gerbers_jlc_prog/` — PROG gerbers for JLCPCB
- `gerbers_jlc_cha/` — CHA gerbers for JLCPCB
- `jlcpcb_order/` — BOM + CPL for assembly
- `neocart_*_cpl_FINAL.csv` — Component placement (final)
- `neocart_*_pos.csv` — Pick and place

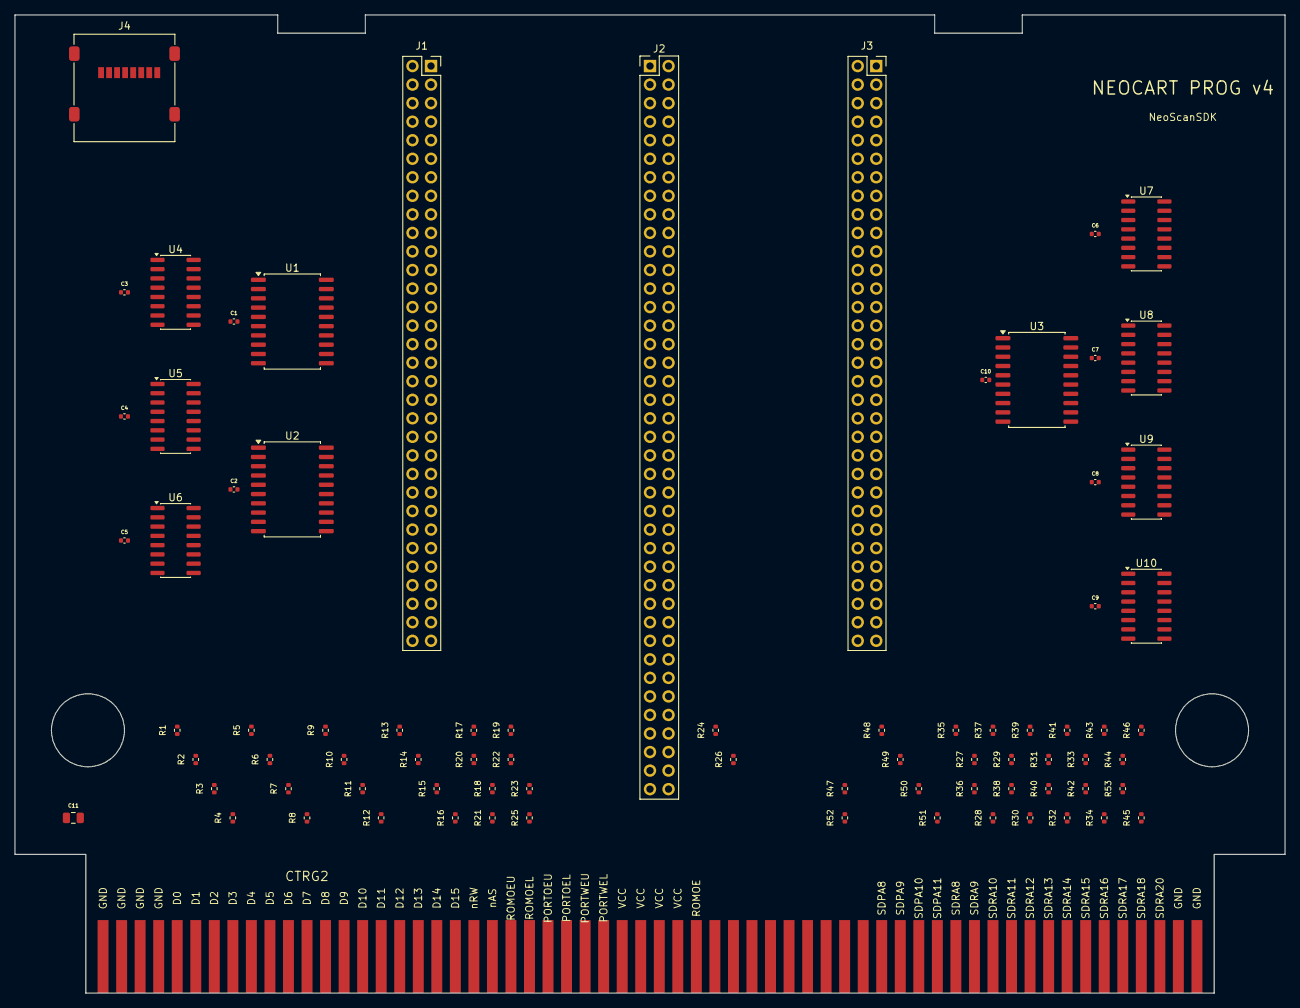
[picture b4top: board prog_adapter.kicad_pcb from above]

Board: 2 copper layers, 174.0 x 134.0 mm, 79 parts (0 on the bottom side), 227 nets, no tracks yet.

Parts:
C1, C2, C3, C4, C5, C6, C7, C8, C9, C10: 100nF; C_0402_1005Metric
C11: 10uF; C_0805_2012Metric
CTRG2: MVS_PROG
J1: FPGA_U2; PinSocket_2x32_P2.54mm_Vertical
J2: TO_CHA; PinHeader_2x40_P2.54mm_Vertical
J3: FPGA_U1; PinSocket_2x32_P2.54mm_Vertical
J4: microSD; microSD_HC_Molex_47219-2001
R1, R2, R3, R4, R5, R6, R7, R8, R9, R10, R11, R12, R13, R14, R15, R16, R17, R18, R19, R20, R21, R22, R23, R24, R25, R26, R27, R28, R29, R30, R31, R32, R33, R34, R35, R36, R37, R38, R39, R40, R41, R42, R43, R44, R45, R46, R47, R48, R49, R50, R51, R52, R53: 470R; R_0402_1005Metric
U1, U2, U3: 74LVC245; SOIC-20W_7.5x12.8mm_P1.27mm
U4, U5, U6, U7, U8, U9, U10: 74HC165; SOIC-16_3.9x9.9mm_P1.27mm

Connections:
4MB: CTRG2.B33, J1.50
68KCLK: CTRG2.B24, R25.1
68KCLK_R: J1.45, R25.2
A1: CTRG2.B5, R1.1
A1_R: R1.2, U4.7
A2: CTRG2.B6, R2.1
A2_R: R2.2, U4.6
A3: CTRG2.B7, R3.1
A3_R: R3.2, U4.5
A4: CTRG2.B8, R4.1
A4_R: R4.2, U4.4
A5: CTRG2.B9, R5.1
A5_R: R5.2, U4.3
A6: CTRG2.B10, R6.1
A6_R: R6.2, U4.13
A7: CTRG2.B11, R7.1
A7_R: R7.2, U4.12
A8: CTRG2.B12, R8.1
A8_R: R8.2, U4.11
A9: CTRG2.B13, R9.1
A9_R: R9.2, U5.7
A10: CTRG2.B14, R10.1
A10_R: R10.2, U5.6
A11: CTRG2.B15, R11.1
A11_R: R11.2, U5.5
A12: CTRG2.B16, R12.1
A12_R: R12.2, U5.4
A13: CTRG2.B17, R13.1
A13_R: R13.2, U5.3
A14: CTRG2.B18, R14.1
A14_R: R14.2, U5.13
A15: CTRG2.B19, R15.1
A15_R: R15.2, U5.12
A16: CTRG2.B20, R16.1
A16_R: R16.2, U5.11
A17: CTRG2.B21, R17.1
A17_R: R17.2, U6.7
A18: CTRG2.B22, R18.1
A18_R: R18.2, U6.6
A19: CTRG2.B23, R19.1
A19_R: R19.2, U6.5
BUF_OE: J1.35, U1.19, U2.19
BUS_DIR: J1.34, U1.1, U2.1
CLK_C: J2.58, J3.46
CLK_P: J1.30, U4.2, U5.2, U6.2
CLK_S: J2.61, J3.49
CLK_SD: J1.41, U7.2, U8.2, U9.2, U10.2
CR0: J2.9, J3.5
CR1: J2.10, J3.6
CR2: J2.11, J3.7
CR3: J2.12, J3.8
CR4: J2.13, J3.9
CR5: J2.14, J3.10
CR6: J2.15, J3.11
CR7: J2.16, J3.12
CR8: J2.17, J3.13
CR9: J2.18, J3.14
CR10: J2.19, J3.15
CR11: J2.20, J3.16
CR12: J2.21, J3.17
CR13: J2.22, J3.18
CR14: J2.23, J3.19
CR15: J2.24, J3.20
CR16: J2.25, J3.21
CR17: J2.26, J3.22
CR18: J2.27, J3.23
CR19: J2.28, J3.24
CR20: J2.29, J3.25
CR21: J2.30, J3.26
CR22: J2.31, J3.27
CR23: J2.32, J3.28
CR24: J2.33, J3.29
CR25: J2.34, J3.30
CR26: J2.35, J3.31
CR27: J2.36, J3.32
CR28: J2.37, J3.33
CR29: J2.38, J3.34
CR30: J2.39, J3.35
CR31: J2.40, J3.36
D0: CTRG2.A5, U1.2
D1: CTRG2.A6, U1.3
D2: CTRG2.A7, U1.4
D3: CTRG2.A8, U1.5
D4: CTRG2.A9, U1.6
D5: CTRG2.A10, U1.7
D6: CTRG2.A11, U1.8
D7: CTRG2.A12, U1.9
D8: CTRG2.A13, U2.2
D9: CTRG2.A14, U2.3
D10: CTRG2.A15, U2.4
D11: CTRG2.A16, U2.5
D12: CTRG2.A17, U2.6
D13: CTRG2.A18, U2.7
D14: CTRG2.A19, U2.8
D15: CTRG2.A20, U2.9
FD0: J1.5, U1.18
FD1: J1.6, U1.17
FD2: J1.7, U1.16
FD3: J1.8, U1.15
FD4: J1.9, U1.14
FD5: J1.10, U1.13
FD6: J1.11, U1.12
FD7: J1.12, U1.11
FD8: J1.13, U2.18
FD9: J1.14, U2.17
FD10: J1.15, U2.16
FD11: J1.16, U2.15
FD12: J1.17, U2.14
FD13: J1.18, U2.13
FD14: J1.19, U2.12
FD15: J1.20, U2.11
FSD0: J1.21, U3.2
FSD1: J1.22, U3.3
FSD2: J1.23, U3.4
FSD3: J1.24, U3.5
FSD4: J1.25, U3.6
FSD5: J1.26, U3.7
FSD6: J1.27, U3.8
FSD7: J1.28, U3.9
GND: C1.2, C2.2, C3.2, C4.2, C5.2, C6.2, C7.2, C8.2, C9.2, C10.2, C11.2, CTRG2.A1, CTRG2.A2, CTRG2.A3, CTRG2.A4, CTRG2.A59, CTRG2.A60, CTRG2.B1, CTRG2.B2, CTRG2.B3, CTRG2.B4, CTRG2.B26, CTRG2.B27, CTRG2.B59, CTRG2.B60, J1.60, J1.62, J1.64, J2.5, J2.6, J2.7, J2.8, J2.74, J2.75, J2.76, J2.77, J2.78, J2.79, J2.80, J3.3, J3.4, J3.60, J3.62, J3.64, J4.3, J4.6, J4.9, U1.10, U2.10, U3.10, U4.8, U4.10, U4.14, U5.8, U5.14, U6.8, U6.14, U7.8, U7.10, U7.14, U8.8, U8.14, U9.8, U9.14, U10.3, U10.4, U10.8, U10.11, U10.12, U10.13, U10.14
LOAD_C: J2.59, J3.47
LOAD_P: J1.31, U4.1, U5.1, U6.1
LOAD_S: J2.62, J3.50
LOAD_SD: J1.42, U7.1, U8.1, U9.1, U10.1
PCK1B: J2.63, J3.51
PCK2B: J2.64, J3.52
PDTACK: CTRG2.B28, J1.48
RESET: CTRG2.B35, R26.1
RESET_R: J1.46, R26.2
ROMOE: CTRG2.A33, R24.1
ROMOEL: CTRG2.A24, R23.1
ROMOEL_R: R23.2, U6.12
ROMOEU: CTRG2.A23, R22.1
ROMOEU_R: R22.2, U6.13
ROMOE_R: J1.32, R24.2, U6.11
ROMWAIT: CTRG2.B25, J1.49
SDD0: J2.41, J3.37
SDD1: J2.42, J3.38
SDD2: J2.43, J3.39
SDD3: J2.44, J3.40
SDD4: J2.45, J3.41
SDD5: J2.46, J3.42
SDD6: J2.47, J3.43
SDD7: J2.48, J3.44
SDMRD: CTRG2.B58, R52.1
SDMRD_CHA: J2.71, J3.53
SDMRD_R: J1.47, R52.2, U10.6
SDPA8: CTRG2.A43, R48.1
SDPA8_R: R48.2, U9.13
SDPA9: CTRG2.A44, R49.1
SDPA9_R: R49.2, U9.12
SDPA10: CTRG2.A45, R50.1
SDPA10_R: R50.2, U9.11
SDPA11: CTRG2.A46, R51.1
SDPA11_R: R51.2, U10.7
SDPAD0: CTRG2.B40, U3.18
SDPAD1: CTRG2.B41, U3.17
SDPAD2: CTRG2.B42, U3.16
SDPAD3: CTRG2.B43, U3.15
SDPAD4: CTRG2.B44, U3.14
SDPAD5: CTRG2.B45, U3.13
SDPAD6: CTRG2.B46, U3.12
SDPAD7: CTRG2.B47, U3.11
SDRA0: CTRG2.B48, R27.1
SDRA0_R: R27.2, U7.7
SDRA1: CTRG2.B49, R28.1
SDRA1_R: R28.2, U7.6
SDRA2: CTRG2.B50, R29.1
SDRA2_R: R29.2, U7.5
SDRA3: CTRG2.B51, R30.1
SDRA3_R: R30.2, U7.4
SDRA4: CTRG2.B52, R31.1
SDRA4_R: R31.2, U7.3
SDRA5: CTRG2.B53, R32.1
SDRA5_R: R32.2, U7.13
SDRA6: CTRG2.B54, R33.1
SDRA6_R: R33.2, U7.12
SDRA7: CTRG2.B55, R34.1
SDRA7_R: R34.2, U7.11
SDRA8: CTRG2.A47, R35.1
SDRA8_R: R35.2, U8.7
SDRA9: CTRG2.A48, R36.1
SDRA9_R: R36.2, U8.6
SDRA10: CTRG2.A49, R37.1
SDRA10_R: R37.2, U8.5
SDRA11: CTRG2.A50, R38.1
SDRA11_R: R38.2, U8.4
SDRA12: CTRG2.A51, R39.1
SDRA12_R: R39.2, U8.3
SDRA13: CTRG2.A52, R40.1
SDRA13_R: R40.2, U8.13
SDRA14: CTRG2.A53, R41.1
SDRA14_R: R41.2, U8.12
SDRA15: CTRG2.A54, R42.1
SDRA15_R: R42.2, U8.11
SDRA16: CTRG2.A55, R43.1
SDRA16_R: R43.2, U9.7
SDRA17: CTRG2.A56, R44.1
SDRA17_R: R44.2, U9.6
SDRA18: CTRG2.A57, R45.1
SDRA18_R: R45.2, U9.5
SDRA19: CTRG2.B57, R46.1
SDRA19_R: R46.2, U9.4
SDRA20: CTRG2.A58, R47.1
SDRA20_R: R47.2, U9.3
SDROE: CTRG2.B56, R53.1
SDROE_R: J1.33, R53.2, U10.5
SD_BUF_OE: J1.43, U3.19
SD_CLK: J1.37, J4.5
SD_CS: J1.36, J4.1
SD_MISO: J1.39, J4.7
SD_MOSI: J1.38, J4.2
SER_C: J2.57, J3.45
SER_P: J1.29, U6.9
SER_S: J2.60, J3.48
SER_SD: J1.40, U10.9
SR1_OUT: U4.9, U5.10
SR2_OUT: U5.9, U6.10
SSR1_OUT: U7.9, U8.10
SSR2_OUT: U8.9, U9.10
SSR3_OUT: U9.9, U10.10
VCC_3V3: C10.1, J1.1, J1.2, J1.3, J1.4, J2.1, J2.2, J3.1, J3.2, J4.4
VCC_5V: C1.1, C2.1, C3.1, C4.1, C5.1, C6.1, C7.1, C8.1, C9.1, C11.1, CTRG2.A29, CTRG2.A30, CTRG2.A31, CTRG2.A32, CTRG2.B29, CTRG2.B30, CTRG2.B31, CTRG2.B32, J1.59, J1.61, J1.63, J2.3, J2.4, J3.59, J3.61, J3.63, U1.20, U2.20, U3.1, U3.20, U4.16, U5.16, U6.16, U7.16, U8.16, U9.16, U10.16
nAS: CTRG2.A22, R21.1
nAS_R: J1.44, R21.2, U6.3
nRW: CTRG2.A21, R20.1
nRW_R: R20.2, U6.4

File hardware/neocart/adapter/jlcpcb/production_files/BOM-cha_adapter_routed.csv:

Comment,Designator,Footprint,LCSC,Quantity
100nF,"C1,C2,C3,C4,C5",C_0402_1005Metric,C1525,5
10uF,C6,C_0805_2012Metric,C15850,1
470R,"R1,R10,R11,R12,R13,R14,R15,R16,R17,R18,R19,R2,R20,R21,R22,R23,R24,R25,R26,R27,R28,R29,R3,R30,R31,R32,R33,R34,R35,R36,R37,R38,R39,R4,R40,R5,R6,R7,R8,R9",R_0402_1005Metric,C25900,40
74HC165,"U1,U2,U3,U4,U5",SOIC-16_3.9x9.9mm_P1.27mm,C5613,5
FROM_PROG,J2,PinHeader_2x40_P2.54mm_Vertical,C5224034,1
